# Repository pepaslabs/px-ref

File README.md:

# PX Ref

This is an LTZ1000-based 7V reference.

Specifically, this is my board layout of a circuit [published](http://www.eevblog.com/forum/metrology/ultra-precision-reference-ltz1000/msg249123/#msg249123) by Andreas (of the EEVBlog forum), which in turn is a modification of the 7V reference circuit from the [datasheet](http://cds.linear.com/docs/en/datasheet/1000afe.pdf).

## Latest revision

- [v2.4.3](kicad/releases/v2.4.3)

## Revision history:

- [v2.4.3](kicad/releases/v2.4.3)
  - Shortened the board very slightly, as the fit in a [TEKO 371.16](http://www.tekoenclosures.com/en/products/family/RF/series/37-39) was just a bit tight.
  - Added two 0.1" holes near LTZ1000 to allow securing a 3D-printed cap.
  - Added more via's in the thermal equalization ring around the LTZ1000.
- [v2.4.2](kicad/releases/v2.4.2)
  - ???
- [v2.4.1](kicad/releases/v2.4.1)
  - Used larger pads on the TO-99 footprint (easier to solder).
  - Moved the input and (buffered) output caps directly onto the board. 
- [v2.4](kicad/releases/v2.4)
  - The board is slightly smaller and fits within a [TEKO 371.16](http://www.tekoenclosures.com/en/products/family/RF/series/37-39) enclosure.
  - The chassis-ground jumper has been removed (these can now be linked with a small wire).
  - The center pin of the R4/R5 divider has been exposed ("T SET") for off-board manipulation.
  - The LTC2057 shutdown pins have been exposed for off-board control.
- [v2.3](kicad/releases/v2.3)
  - The "b" variant has been merged back into a single board design (R4, R5 and R45 are now all on the same board design).
  - The LTC2057 shutdown pins are now left floating.
- [v2.2](kicad/releases/v2.2), [v2.2b](kicad/releases/v2.2b)
  - 2.2 uses a single divider footprint (called R45) for R4 and R5.
  - 2.2b uses separate footprints for R4 and R5.
  - An output buffer was added (LTC2057).
  - **Errata:**
    - A mistake was made with the LTC2057 shutdown pins which will result in self-heating of a few degrees in the LTC2057.  The work-around is to disconnect pins 1 and 8 of the LTC2057. 
- [v2.1](kicad/releases/v2.1)
  - Added a jumper to optionally link GND to a chassis standoff.
  - Used smaller capacitor footprints.
  - Exposed the star ground as a solderable terminal.
  - Switched D1 from a 1N4001 to a 1N4148.
  - Used smaller footprints for D1 and D2.
  - **Errata:**
    - Andreas capacitor C15 was accidentally left off of this board design.  This cap isn't critical, but a work-around is to bodge a 0.1uF cap across pins 5-6 of the LT1013.
- [v2](kicad/releases/v2)
  - Switched to a simpler, 2-layer, 50mm x 50mm board design.
- [v1](kicad/releases/v1)
  - First design.  4-layer with via stitching for a mild EMI shielding effect.
  - This board was never ordered and tested.

## Schematic

Andreas' original schematic: [png](media/LTZ1KA_1b.PNG)

My adapted version of Andreas' schematic: [pdf](kicad/releases/v2.4.1/basic-ltz1000.pdf)

## Purchasing

You can order a copy of this board from OSHPark: [link](https://oshpark.com/shared_projects/hUZKe65r)

## Discussion

My posts to the EEVBlog forum about this design: [link](http://www.eevblog.com/forum/metrology/ultra-precision-reference-ltz1000/msg1375209/#msg1375209) [link](http://www.eevblog.com/forum/metrology/px-reference/)

The naming of this board was inspired by other LTZ1000 references: [KX](https://xdevs.com/article/kx-ref/), [FX](https://xdevs.com/article/792x/), [MX](https://www.eevblog.com/forum/metrology/mx-reference/), [CX](https://www.eevblog.com/forum/metrology/cx-reference/), [QX](http://www.eevblog.com/forum/metrology/ultra-precision-reference-ltz1000/msg1377719/#msg1377719)

See also:
- https://github.com/pepaslabs/dr-frank-ltz1000
- https://github.com/pepaslabs/hp-03458-66509-clone

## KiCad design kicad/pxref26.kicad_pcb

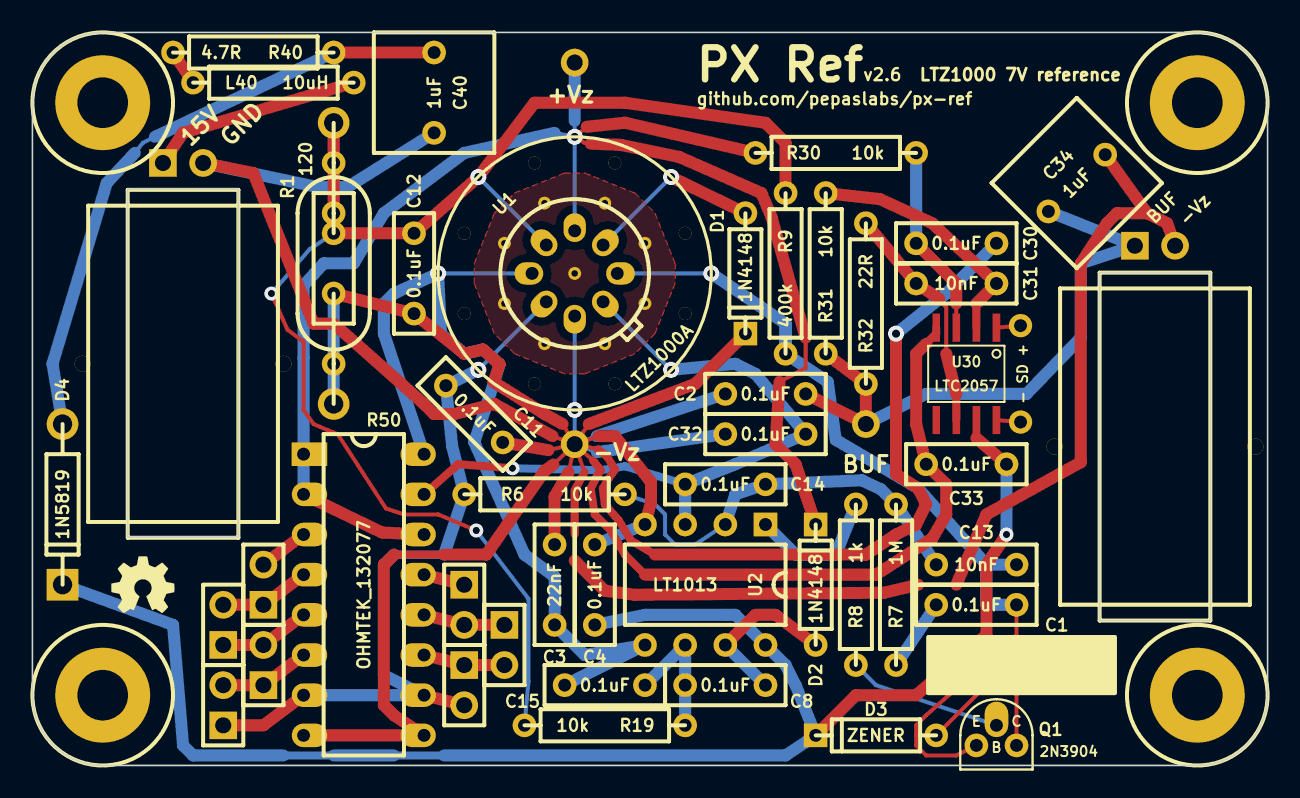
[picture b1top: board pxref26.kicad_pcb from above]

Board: 2 copper layers, 78.1 x 46.4 mm, 71 parts (0 on the bottom side), 31 nets.

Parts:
C1, C2, C4, C8, C11, C12, C14, C15, C30, C32, C33: 0.1uF; BOXCAP_01_03_02_059A
C3: 22nF; BOXCAP_01_03_02_059A
C13, C31: 10nF; BOXCAP_01_03_02_059A
C34, C40: 1uF; BOXCAP_02_03_03_059A
D1, D2: 1N4148; DIODE_SS_059A_03_PL
D3: ZENER; DIODE_SS_059A_03_PL
D4: 1N5819; DIODE_1A_069A_04_PL
H1: HOLE; hole_M3
H***: Val**; hole_M3
H***#2, H***#3, H***#15, H***#16, H***#17, H***#18, H***#19, H***#20, H***#21, H***#22: Val**; 1pin_032_058
H***#4, H***#5, H***#6, H***#7, H***#8, H***#9, H***#10, H***#11, H***#12: Val**; Via_016
H***#13, H***#14: Val**; hole_M3
JP3, JP5, JP50, JP51, JP52, JP54, JP56: JUMPER2; SIL-2
L40: 10uH; R_AXIAL_0W25_059A_PL
P1, P6: CONN_2X1; ferrite_core_20x12_PL
P2, P3, P5: CONN_1X1; 1pin_040_069
Q1: 2N3904; TO-92_Q_EBC_059Bo_PL
R1: 120; R_BOX_HERMETIC_WW_AXIAL_07_PL
R6, R19, R30, R31: 10k; R_AXIAL_0W25_059A_PL
R7: 1M; R_AXIAL_0W25_059A_PL
R8: 1k; R_AXIAL_0W25_059A_PL
R9: 400k; R_AXIAL_0W25_059A_PL
R32: 22R; R_AXIAL_0W25_059A_PL
R40: 4.7R; R_AXIAL_0W25_059A_PL
R50: OHMTEK_132077; DIP16_PL
U1: LTZ1000A; TO-99_PL
U2: LT1013; DIP8_059A_PL
U30: LTC2057; SO-8

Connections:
15V: C4.1, C33.1, D3.2, D4.2, U2.8, U30.7
CHASSIS: H1.1, H***#4.~, H***#5.~, H***#6.~, H***#7.~, H***#8.~, H***#9.~, H***#10.~, H***#11.~, H***#12.~
H+: C1.2, C13.1, Q1.1, R9.2, U1.1
unnamed: L40.1, R40.2
unnamed: L40.2, P1.1
unnamed: C40.1, D4.1, R40.1
unnamed: JP54.1, JP56.2, R50.6
unnamed: C30.1, R30.2, U30.3
unnamed: C31.2, R32.1, U30.6
unnamed: C31.1, R31.1, U30.2
unnamed: JP3.1, JP51.2, R50.12
unnamed: JP51.1, R50.13
unnamed: JP52.1, JP54.2, R50.5
unnamed: JP50.1, JP52.2, R50.4
unnamed: JP50.2, R50.3
unnamed: JP3.2, JP5.1, R50.11
unnamed: C8.2, D2.1, U2.7
unnamed: C1.1, R7.1
unnamed: R8.1, U2.1
unnamed: D3.1, Q1.3
unnamed: Q1.2, R8.2
unnamed: D1.1, U1.2
unnamed: C12.1, R1.1, R9.1, R19.2, U1.4
unnamed: C13.2, C14.1, R6.2, R7.2, U2.2
unnamed: C8.1, C15.1, R19.1, U2.6
R2H: D2.2, P2.1, R30.1, R50.1, R50.2, R50.14, U1.3
R2L: C3.1, C15.2, R50.16, U1.5, U2.5
R3L: C2.1, C14.2, R50.15, U1.8, U2.3
R4L: C11.1, JP5.2, JP56.1, R6.1, R50.7, R50.10, U1.6
R5L: C2.2, C3.2, C4.2, C11.2, C12.2, C30.2, C32.2, C33.2, C34.2, C40.2, D1.2, P1.2, P5.1, P6.2, R1.2, R50.8, R50.9, U1.7, U2.4, U30.4
Vz+ Buf: C32.1, C34.1, P3.1, P6.1, R31.2, R32.2

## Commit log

2017-12-17 pulling in Andreas circuit
2017-12-21 adding media
2017-12-21 adding png version of schematic
2017-12-21 adding BOM graphic
2017-12-22 pulling in updated parts
2017-12-27 Updating footprints for caps and diodes
2017-12-27 reroute WIP
2017-12-29 v2.1 gerbers
2017-12-29 adding v2.1 board renders
2017-12-29 adding v2.1 kicad shots
2017-12-29 v2.2 gerbers
2017-12-29 adding v2.2 board renders
2017-12-29 v2.2 revisions
2017-12-29 updated v2.2 board renders
2017-12-29 fixing output buffer, adding copper zones
2017-12-29 updating v2.2 board renders
2017-12-29 Updating README
2017-12-29 forgot the bottom copper board render
2018-01-23 2.2b
2018-01-23 2.2b board shots
2018-02-04 adding BOM and README for v2.2
2018-02-04 v2.2b readme
2018-02-04 readme
2018-02-04 adding board shots
2018-02-15 v2.4 gerbers
2018-02-16 silkscreen typo
2018-02-16 board shots
2018-02-16 typo
2018-04-29 v2.4.1
2018-04-29 updating readmes
2018-06-24 adding vias
2018-06-24 v2.4.2
2018-06-24 branching files for 2.5.x
2018-06-25 splitting design into v2.4.x and v2.5.x
2018-06-27 2.6 schematic
2018-06-29 v2.6
2018-06-29 ohmtek script
2018-06-29 renaming board edge files to work with JLCPCB
2018-06-29 v2.4.2 board shots
2018-06-29 board shots v2.4.2
2018-06-29 board shots v2.6
2018-06-29 board shots v2.5
2018-07-02 updated parts
2022-08-30 v2.4.3
